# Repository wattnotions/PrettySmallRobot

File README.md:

[Watch the video here](https://www.youtube.com/watch?v=d6PTFtglKmE&feature=youtu.be)

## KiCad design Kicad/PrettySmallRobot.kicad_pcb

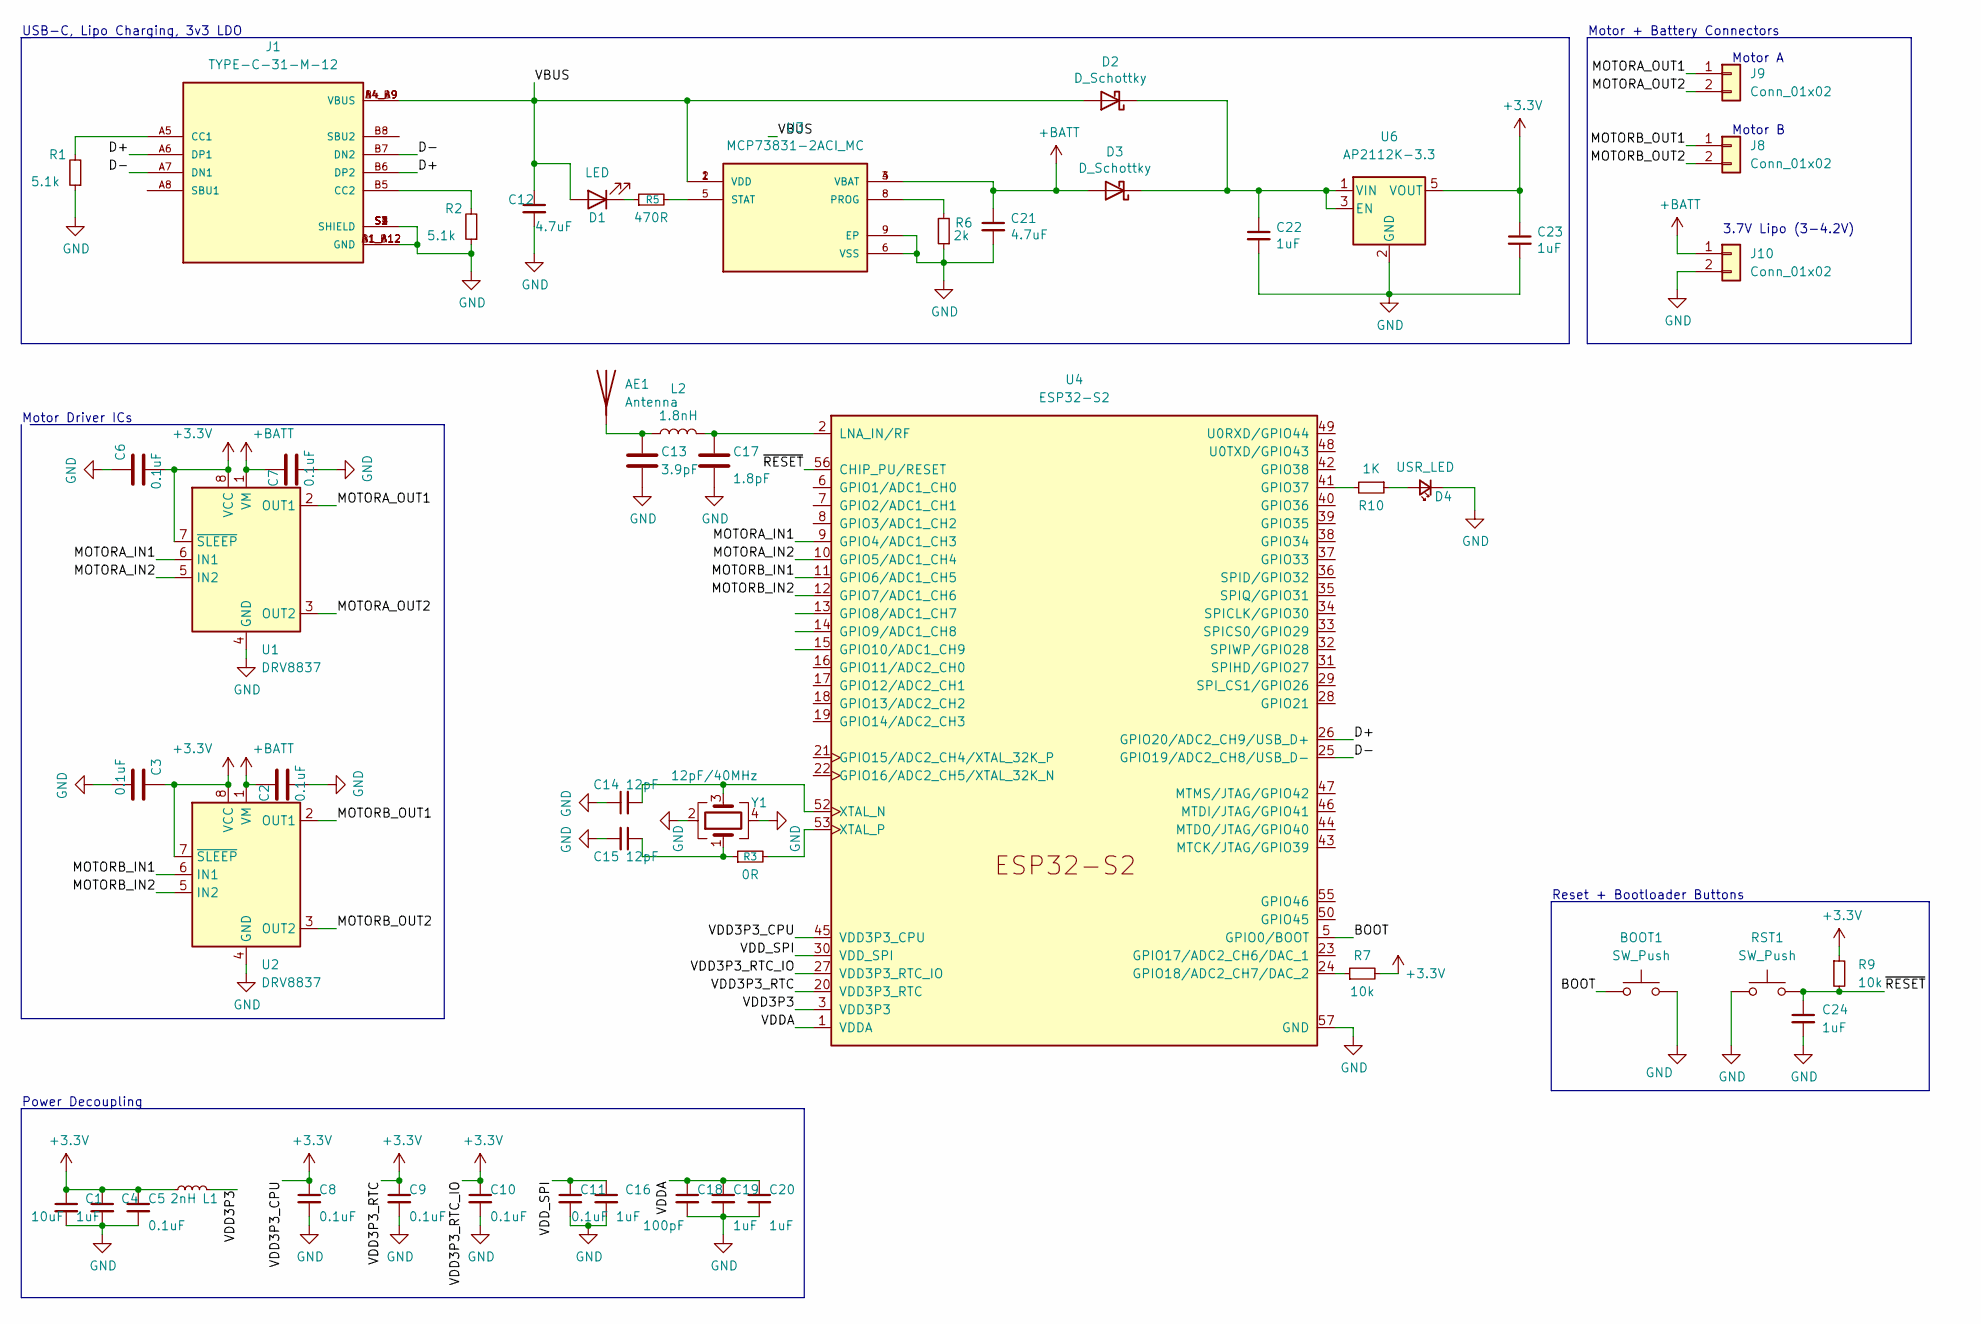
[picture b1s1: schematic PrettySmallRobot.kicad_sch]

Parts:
AE1: Antenna; C_1206_3216Metric; LCSC C293767
BOOT1: SW_Push; SW_SPST_B3U-1000P; LCSC C231329
C1: 10uF; C_0603_1608Metric
C2, C3, C5, C6, C7, C8, C9, C10, C11: 0.1uF; C_0402_1005Metric
C4, C16, C19, C20, C22, C23, C24: 1uF; C_0402_1005Metric
C12, C21: 4.7uF; C_0402_1005Metric
C13: 3.9pF; C_0402_1005Metric; LCSC C313081
C14, C15: 12pF; C_0402_1005Metric; LCSC C1547
C17: 1.8pF; C_0402_1005Metric; LCSC C140677
C18: 100pF; C_0402_1005Metric
D1: LED; LED_0402_1005Metric
D2, D3: D_Schottky; D_SOD-323; LCSC C146335
D4: USR_LED; LED_0402_1005Metric
J1: TYPE-C-31-M-12; HRO_TYPE-C-31-M-12; PARTREV 2020.12.08; LCSC C165948
J8, J9, J10: Conn_01x02; JST_PH_S2B-PH-K_1x02_P2.00mm_Horizontal
L1: 2nH; L_0402_1005Metric
L2: 1.8nH; L_0402_1005Metric; LCSC C87530
R1, R2: 5.1k; R_0402_1005Metric
R3: 0R; R_0402_1005Metric
R5: 470R; R_0402_1005Metric
R6: 2k; R_0402_1005Metric
R7, R9: 10k; R_0402_1005Metric
R10: 1K; R_0402_1005Metric
RST1: SW_Push; SW_SPST_B3U-1000P; LCSC TSA363G25-250B
U1, U2: DRV8837; WSON-8-1EP_2x2mm_P0.5mm_EP0.9x1.6mm; LCSC C191000
U3: MCP73831-2ACI_MC; SON50P200X300X100-9N; PARTREV G; LCSC C150772
U4: ESP32-S2; QFN-56-1EP_7x7mm_P0.4mm_EP5.6x5.6mm; LCSC C529594
U6: AP2112K-3.3; SOT-23-5; LCSC C3021085
Y1: 12pF/40MHz; Crystal_SMD_3225-4Pin_3.2x2.5mm; LCSC C252255

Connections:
+3V3: C1.1, C3.1, C4.1, C5.1, C6.1, C8.1, C9.1, C10.1, C23.1, L1.1, R7.2, R9.1, U1.7 (~SLEEP), U1.8 (VCC), U2.7 (~SLEEP), U2.8 (VCC), U4.20 (VDD3P3_RTC), U4.27 (VDD3P3_RTC_IO), U4.45 (VDD3P3_CPU), U6.5 (VOUT)
+BATT: C2.1, C7.1, C21.1, D3.2 (A), J10.1, U1.1 (VM), U2.1 (VM), U3.3 (VBAT), U3.4 (VBAT)
/BOOT: BOOT1.1, U4.5 (GPIO0/BOOT)
/D+: J1.A6 (DP1), J1.B6 (DP2), U4.26 (GPIO20/ADC2_CH9/USB_D+)
/D-: J1.A7 (DN1), J1.B7 (DN2), U4.25 (GPIO19/ADC2_CH8/USB_D-)
/MOTORA_IN1: U1.6 (IN1), U4.9 (GPIO4/ADC1_CH3)
/MOTORA_IN2: U1.5 (IN2), U4.10 (GPIO5/ADC1_CH4)
/MOTORA_OUT1: J9.1, U1.2 (OUT1)
/MOTORA_OUT2: J9.2, U1.3 (OUT2)
/MOTORB_IN1: U2.6 (IN1), U4.11 (GPIO6/ADC1_CH5)
/MOTORB_IN2: U2.5 (IN2), U4.12 (GPIO7/ADC1_CH6)
/MOTORB_OUT1: J8.1, U2.2 (OUT1)
/MOTORB_OUT2: J8.2, U2.3 (OUT2)
/VBUS: C12.1, D1.2 (A), D2.2 (A), J1.A4_B9 (VBUS), J1.B4_A9 (VBUS), U3.1 (VDD), U3.2 (VDD)
/VDD3P3: L1.2, U4.3 (VDD3P3), U4.4 (VDD3P3)
/VDDA: C18.1, C19.1, C20.1, U4.1 (VDDA), U4.51 (VDDA), U4.54 (VDDA)
/VDD_SPI: C11.1, C16.1, U4.30 (VDD_SPI)
/~RESET: C24.1, R9.2, RST1.2, U4.56 (CHIP_PU/RESET)
GND: BOOT1.2, C1.2, C2.2, C3.2, C4.2, C5.2, C6.2, C7.2, C8.2, C9.2, C10.2, C11.2, C12.2, C13.2, C14.1, C15.2, C16.2, C17.2, C18.2, C19.2, C20.2, C21.2, C22.2, C23.2, C24.2, D4.1 (K), J1.A1_B12 (GND), J1.B1_A12 (GND), J1.S1 (SHIELD), J1.S2 (SHIELD), J1.S3 (SHIELD), J1.S4 (SHIELD), J10.2, R1.1, R2.1, R6.1, RST1.1, U1.4 (GND), U1.9 (GND), U2.4 (GND), U2.9 (GND), U3.6 (VSS), U3.9 (EP), U4.57 (GND), U6.2 (GND), Y1.2, Y1.4
unnamed: AE1.1 (A), C13.1, L2.1
unnamed: C14.2, U4.52 (XTAL_N), Y1.3
unnamed: C15.1, R3.1, Y1.1
unnamed: C17.1, L2.2, U4.2 (LNA_IN/RF)
unnamed: C22.1, D2.1 (K), D3.1 (K), U6.1 (VIN), U6.3 (EN)
unnamed: D1.1 (K), R5.1
unnamed: D4.2 (A), R10.1
unnamed: J1.A5 (CC1), R1.2
unnamed: J1.B5 (CC2), R2.2
unnamed: R3.2, U4.53 (XTAL_P)
unnamed: R5.2, U3.5 (STAT)
unnamed: R6.2, U3.8 (PROG)
unnamed: R7.1, U4.24 (GPIO18/ADC2_CH7/DAC_2)
unnamed: R10.2, U4.41 (GPIO37)

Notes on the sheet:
Reset + Bootloader Buttons
USB-C, Lipo Charging, 3v3 LDO
Motor A
Power Decoupling
Motor B
3.7V Lipo (3-4.2V)
Motor Driver ICs
Motor + Battery Connectors

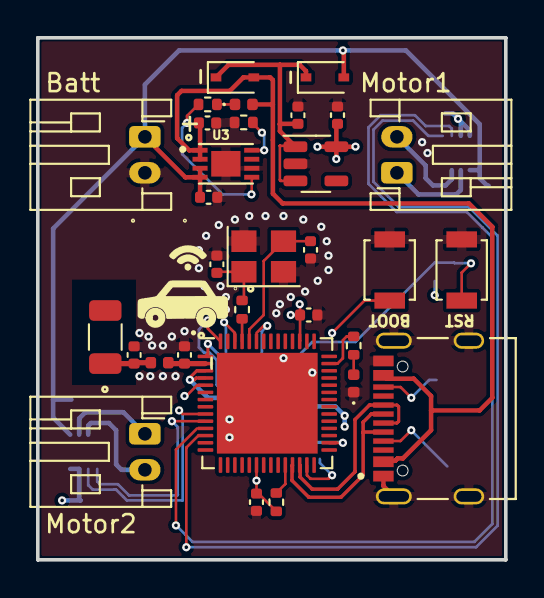
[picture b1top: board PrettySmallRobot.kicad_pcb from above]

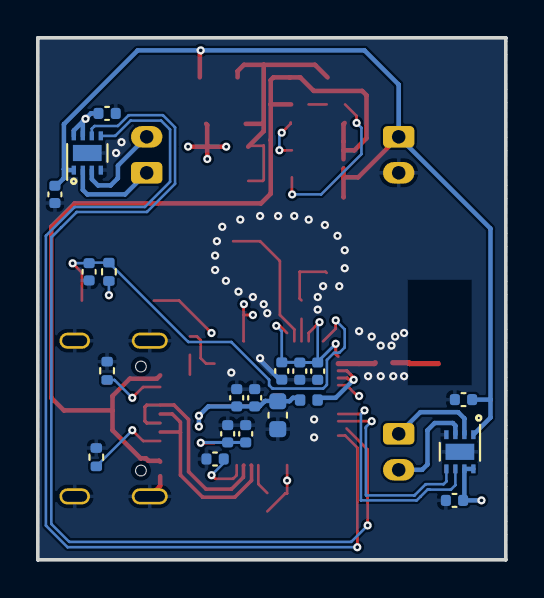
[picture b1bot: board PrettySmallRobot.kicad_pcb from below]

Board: 4 copper layers, 26.0 x 29.0 mm, 51 parts (20 on the bottom side), 33 nets.

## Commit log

2023-01-12 1ST COMMIT
2023-01-12 added antenna match circuit
2023-01-12 schematic progressed
2023-01-12 added adafruit ref diagram
2023-01-12 progressed schematic
2023-01-14 usb c nets done, started on esp32 nets
2023-01-14 progressed esp32 schem nets
2023-01-14 cleaned up schematic - added boxes around sections etc
2023-01-14 worked on motor driver signals
2023-01-14 added testpoint on 3v3
2023-01-15 removed pullups on driver enable signals
2023-01-15 added pi matching network vals + lcsc numbers
2023-01-15 matched 90% of parts with footprints
2023-01-15 preliminary floorplanning done
2023-01-17 replaced 3.3v ldo with ap2112k
2023-01-17 replaced jst connectors with smd solder pads
2023-01-17 routing bout 70% done
2023-01-18 routed motor driver sigs
2023-01-18 fixed drc issues
2023-01-18 àdded car graphic
2023-01-27 ripped up all routing to start again to fit the new cad
2023-01-28 resized board to 29x27mm
2023-01-28 resized board again to 29x26mm
2023-01-28 re added jst connectors, removed mount holes
2023-01-28 added keeput area for clip sections
2023-01-28 floorplanning 50% done
2023-01-28 routing started
2023-01-28 swapped motor a and b connectors
2023-01-28 all nets routed, drc done
2023-01-29 changed mcp 73831 to diff package in stock on jlcpcb
2023-03-03 update to latest
2023-03-03 added some motor control code
2023-03-05 added mqtt remote control stuff
2023-03-12 made server side robot wheel mqtt script
2023-03-12 firimware to accept mqtt commads from wheel, working
2023-03-14 changed adc cut of val to 100
2023-03-14 added variable sterring code
2023-03-26 re-arraned folder structure
